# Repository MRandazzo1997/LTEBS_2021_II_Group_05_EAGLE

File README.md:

# LTEBS_2021_II_Group_05_EAGLE
We set the trace width to 8mils near the MUX, except for power signals, since the clearance between copper element should be of 6mils. 
Given the small size of MUX pads, a trace width of 10mils wouldn't allow the correct distancing.

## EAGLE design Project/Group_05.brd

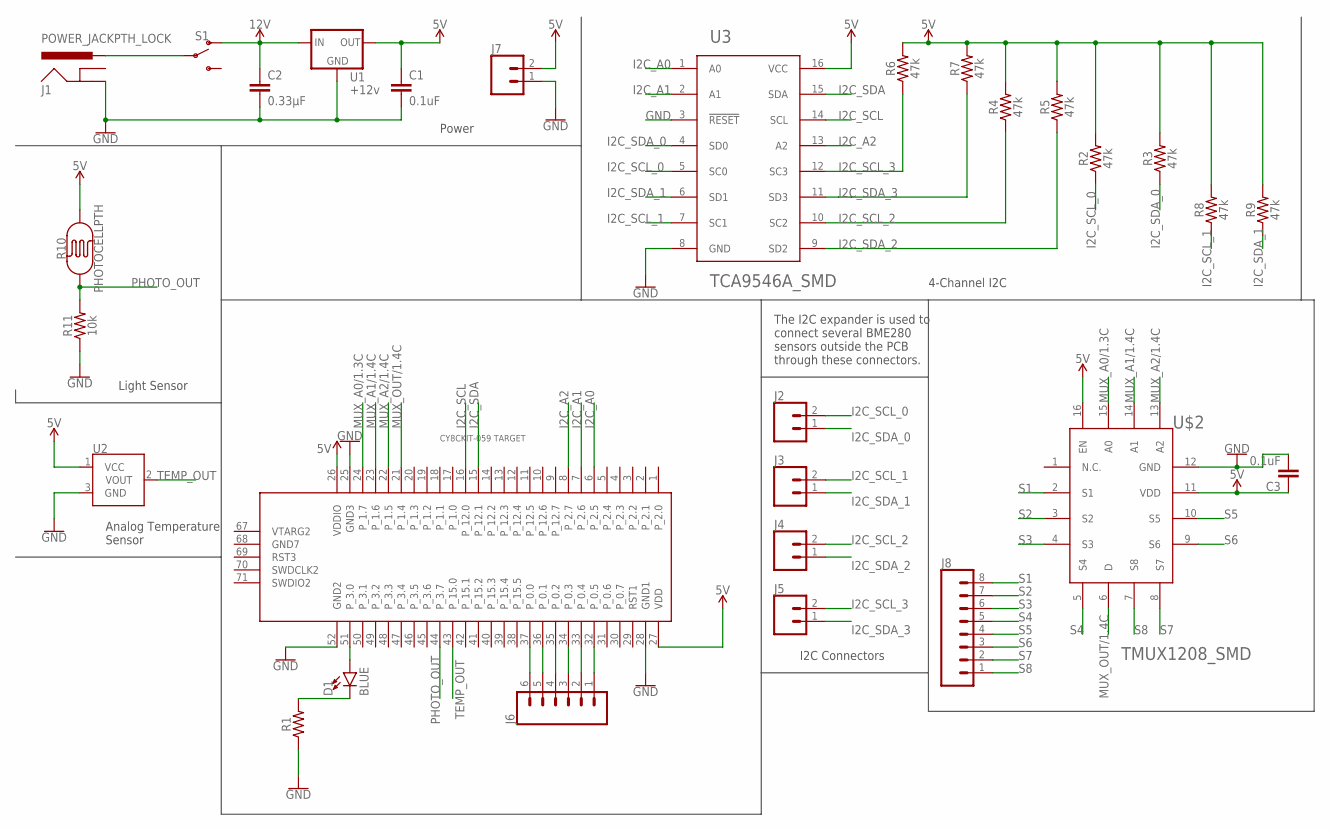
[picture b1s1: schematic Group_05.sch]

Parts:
C1, C3: 0.1uF; CAP-PTH-SMALL-KIT
C2: 0.33µF; 0805
D1: BLUE; LED-1206
J1: POWER_JACKPTH_LOCK; POWER_JACK_PTH_LOCK
J2, J3, J4, J5, J7: CONN_02; 1X02
J6: CONN_06LOCK; 1X06_LOCK
J8: CONN_08LOCK; 1X08_LOCK
R1: AXIAL-0.3
R2, R3, R4, R5, R6, R7, R8, R9: 47k; 0603
R10: PHOTOCELLPTH; PHOTOCELL
R11: 10k; 0603
S1: SWITCH-SPDT-PTH-11.6X4.0MM; SWITCH_SPDT_PTH_11.6X4.0MM
U1: +12v; TO-252
U2: TMP36GT9; TO-92
U3: TCA9546A_SMD; TSSOP16
U$1: CY8CKIT-059_TARGET
U$2: TMUX1208_SMD; QFN16

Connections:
5V: C1.1, C3.1, J7.2, R2.2, R3.2, R4.2, R5.2, R6.2, R7.2, R8.2, R9.2, R10.2, U1.2 (OUT), U2.1 (VCC), U3.16 (VCC), U$1.26 (VDDIO), U$1.27 (VDD), U$2.11 (VDD), U$2.16 (EN)
12V: C2.1, S1.1 (O), U1.1 (IN)
GND: C1.2, C2.2, C3.2, J1.GND, J7.1, R1.P$1 (1), R11.1, U1.3 (GND), U2.3 (GND), U3.3 (!RESET), U3.8 (GND), U$1.25 (GND3), U$1.28 (GND1), U$1.52 (GND2), U$2.12 (GND)
I2C_A0: U3.1 (A0), U$1.6 (P_2.5)
I2C_A1: U3.2 (A1), U$1.7 (P_2.6)
I2C_A2: U3.13 (A2), U$1.8 (P_2.7)
I2C_SCL: U3.14 (SCL), U$1.16 (P_12.0)
I2C_SCL_0: J2.2, R2.1, U3.5 (SC0)
I2C_SCL_1: J3.2, R8.1, U3.7 (SC1)
I2C_SCL_2: J4.2, R4.1, U3.10 (SC2)
I2C_SCL_3: J5.2, R6.1, U3.12 (SC3)
I2C_SDA: U3.15 (SDA), U$1.15 (P_12.1)
I2C_SDA_0: J2.1, R3.1, U3.4 (SD0)
I2C_SDA_1: J3.1, R9.1, U3.6 (SD1)
I2C_SDA_2: J4.1, R5.1, U3.9 (SD2)
I2C_SDA_3: J5.1, R7.1, U3.11 (SD3)
MUX_A0/1.3C: U$1.24 (P_1.7), U$2.15 (A0)
MUX_A1/1.4C: U$1.23 (P_1.6), U$2.14 (A1)
MUX_A2/1.4C: U$1.22 (P_1.5), U$2.13 (A2)
MUX_OUT/1.4C: U$1.21 (P_1.4), U$2.6 (D)
unnamed: J6.6, U$1.37 (P_0.0)
unnamed: D1.A, U$1.51 (P_3.0)
unnamed: J1.PWR, S1.2
unnamed: D1.C, R1.P$2 (2)
unnamed: J6.5, U$1.36 (P_0.1)
unnamed: J6.4, U$1.35 (P_0.2)
unnamed: J6.3, U$1.34 (P_0.3)
unnamed: J6.2, U$1.33 (P_0.4)
unnamed: J6.1, U$1.32 (P_0.5)
PHOTO_OUT: R10.1, R11.2, U$1.44 (P_3.7)
S1: J8.8, U$2.2 (S1)
S2: J8.7, U$2.3 (S2)
S3: J8.6, U$2.4 (S3)
S4: J8.5, U$2.5 (S4)
S5: J8.4, U$2.10 (S5)
S6: J8.3, U$2.9 (S6)
S7: J8.2, U$2.8 (S7)
S8: J8.1, U$2.7 (S8)
TEMP_OUT: U2.2 (VOUT), U$1.43 (P_15.0)

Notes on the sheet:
Power
Light Sensor
Analog Temperature Sensor
4-Channel I2C
The I2C expander is used to connect several BME280 sensors outside the PCB through these connectors.
I2C Connectors

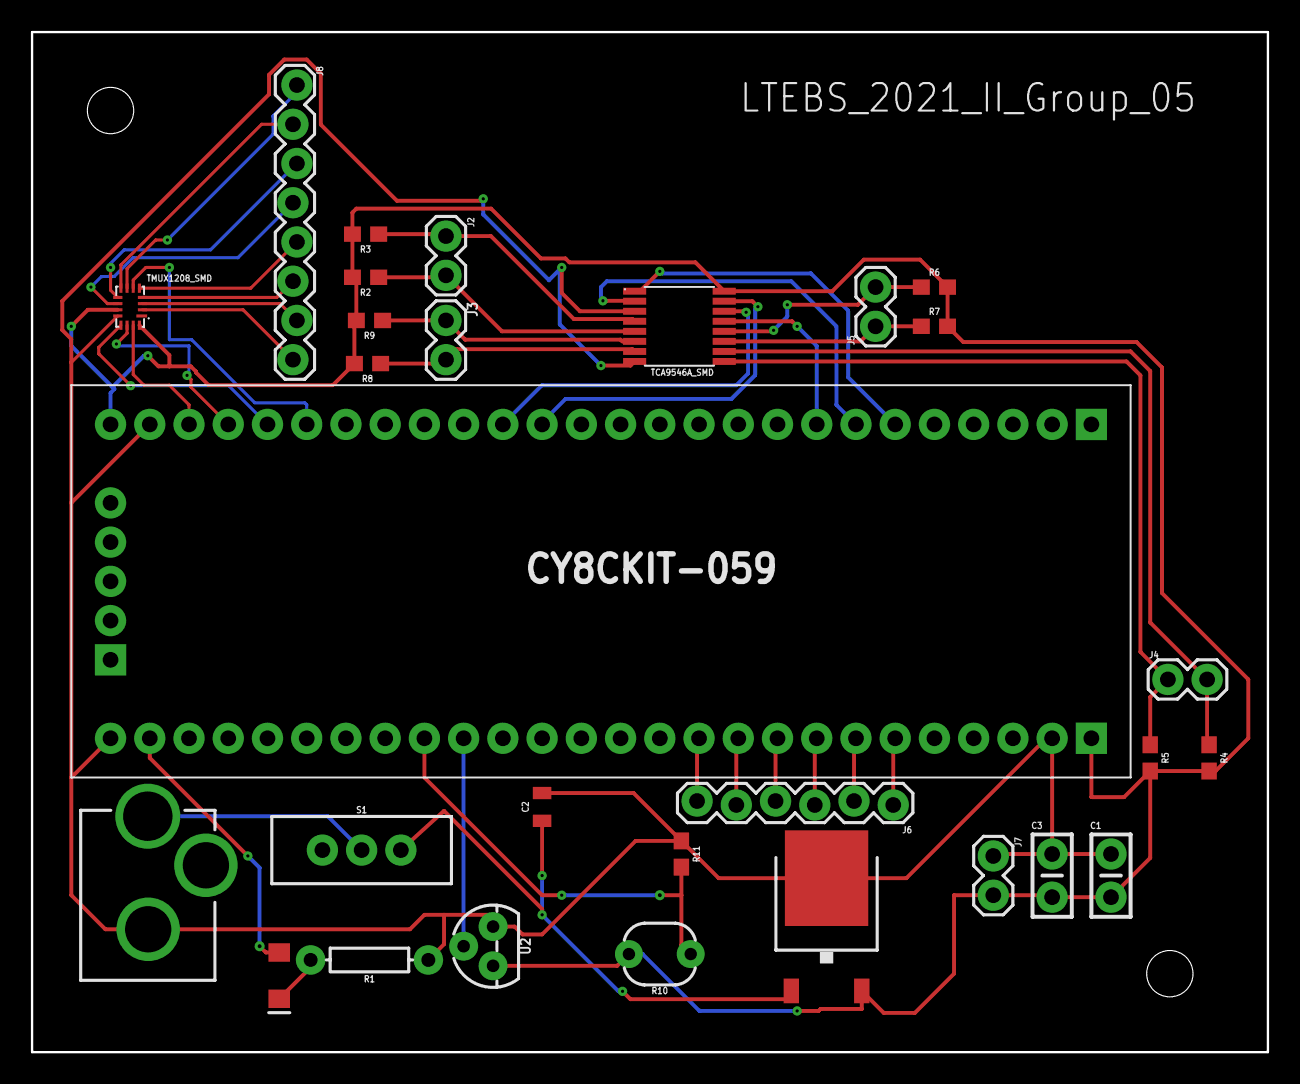
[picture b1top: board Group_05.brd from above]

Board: 2 copper layers, 80.0 x 66.0 mm, 29 parts (0 on the bottom side), 39 nets.

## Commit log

2021-03-18 Library 1st commit
2021-03-18 Second Library commit
2021-03-18 Library third commit
2021-03-18 Schematic first commit
2021-03-18 Second schematic commit
2021-03-18 Third schematic commit
2021-03-18 4th schematic commit (completed?)
2021-03-19 Design Rules
2021-03-19 modifica schematico
2021-03-20 Board commit
2021-03-21 brd placement
2021-03-21 Reduced dimensions
2021-03-22 Holes, copper pour
2021-03-22 Silkscreen and trace resize
2021-03-24 Width 8 mils
2021-03-26 Final
2021-03-26 Final Version

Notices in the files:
parts and their libraries:
SparkFun-Capacitors: Licensing: Creative Commons ShareAlike 4.0 International - https://creativecommons.org/licenses/by-sa/4.0
